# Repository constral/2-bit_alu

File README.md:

# 2-Bit Arithmetic Logic Unit with 4 Operations

<image src="picture.jpeg" width="800px"/>

## 1. Description

This 2-bit ALU (Arithmetic Logic Unit) is built using 74-series logic gates and multiplexers, and performs four basic operations: Logical AND, Logical OR, Addition, and positive-result Subtraction, on two 2-bit input words (A1A0 and B1B0). It uses a 2-bit opcode (I1I0) to select the operation, and displays the result as a 3-bit output (R2R1R0). Logical AND and OR operate only on the least significant bits (A0 and B0), with the result being displayed on R0. Arithmetic operations use the full words on input and output, and the output R2 is reserved for indicating overflow during addition.

## 2. Block Schematic
<image src="block.png" width="600px"/>

## 3. Logical Schematic and Simulation
Logisim Evolution was used for the prototyping of the circuit and for simulating its functionality. (file provided in repository)
<image src="logical.png" width="1000px"/>

## 4. Electrical Schematic and PCB
The project’s schematic and PCB were designed in KiCAD. (files provided in repository)
<image src="schematic.png" width="1000px"/>
<image src="pcb.png" width="800px"/>

## 5. Operation
The ALU takes two 2-bit words (A1A0 and B1B0) as input for its operations, and one 2-bit word (I1I0) for selecting the opcode. The results of the operations are displayed using LEDs in the form of a 3-bit word (R2R1R0). The operations and their opcodes are as follows:
<br>
<br>Logical AND		00
<br>Logical OR		01
<br>Addition		10
<br>Subtraction		11
<br>
<br>For the logical operations, only the least significant bits of the inputs - A0 and B0 - are operated upon, and the result is displayed on the result bit R0. The arithmetic operations employ the full 2-bit input word as well as two output bits, R1 and R0, while the third, R2, is reserved for displaying overflows from summations, and will remain LOW otherwise.

## 6. In-depth analysis of functionality
The general idea is that the input words A and B are forwarded to the operation-performing combinatorial logic gate circuits. Several multiplexers then select from among the results of the gate arrays, and based on the instruction opcode, the result of an operation is displayed. There are two arrays of multiplexers, corresponding to the 2-bit instruction word - I1 selects the arithmetic operations if 1, or the logic operations if 0. I0 further differentiates between the AND/OR, and SUM/DIFF operations.
<br>The logic unit is quite simple, being composed of just an AND and an OR gate, handling the AND and OR operations, respectively. Both gates are active at the same time - the desired result is chosen using a 2-input multiplexer.
<br>The arithmetic unit uses a 2-bit carry-lookahead adder (CLA for short) to perform addition and subtraction. The CLA adder works by taking 5 inputs - one for the carry-in of the summation of the LSB digits, as well as 4 more inputs consisting of the two 2-bit input words, A and B. The adder then outputs bits labeled to be the “sum” of each pair digits.

#### Timing considerations and adders
Generally, addition can be implemented with full adders, which work by taking as inputs two operators A, B, and a third input for the carry-in of the summation, and give as outputs one bit as the sum of the digits, and a second, which acts as the carry for a cascading summation. One full adder adds together one pair of digits, and many can be put in a cascading connection to produce a ripple-carry adder.
<br>Initially, the design of this ALU employed, for its arithmetic unit, two full adders with ripple carry, rather than a CLA adder. Upon further analysis, however, it was determined that the two full adders, which operated without any synchronicity signal from a clock (the only way of avoiding timing issues with such a design), would have produced wrong results due to timing issues caused by propagation delays inherent in the logic gates. A pseudo-timing diagram follows:
<image src="logi_wrong.png" width="1000px"/>
As can be seen from the schematic, the ripple-carry is sent from the first adder when the gate U4C fires its output, namely, in the 5th time period. This carry is meant to arrive at gate U3D – however, U3D fires in the 4th period, just before U4C, from which it is meant to receive its input. This is an obvious problem – U3D’s output will not account for the carry it was supposed to receive, since gate U4C had no time to send its output just yet.
<image src="logi_cla.png" width="1000px"/>
For a carry lookahead adder, however, no such issue exists – instead of waiting for the adders of less significant digits to finish their execution and send a ripple carry, the CLA adder uses extra logic circuitry that determines, based on the digits in the input words, whether a carry will be generated, before the adders dealing with said digits finish their execution. This absolves each individual adder of their dependency upon previous adder stages, allowing every individual pair to be summed up at the same time as, and without having to wait for, the others.
<br>The design principle of the CLA adder is the avoidance of successive propagation, by predicting whether an operation will give a carry, before the operation occurs in the first place. This is done by introducing extra logic gates into the design, accounting for all possible situations that could result in a stage receiving a carry. Whether one of the adder stages in a CLA adder receives a carry depends on whether a previous stage has either generated a carry by itself, or propagated one from a stage before it. This ALU implements a 2-bit CLA adder, so the situations that it accounts for w.r.t. each carry are:

Carry-out 0:
- do A0 and B0 generate a carry?
- is there a carry (generated externally) AND A0 and B0 propagate it?

Carry-out 1:
- do A1 and B1 generate a carry?
- is there a carry (generated by A0 and B0) AND A1 and B1 propagate it?
- is there a carry (generated externally) AND A0 and B0 propagate it AND A1 and B1 propagate it?

To further illustrate the principle, if we had to implement a 3-bit CLA adder, we would also have accounted for:

Carry-out 2:
- do A2 and B2 generate a carry?
- is there a carry (generated by A1 and B1) AND A2 and B2 propagate it?
- is there a carry (generated by A0 and B0) AND A1 and B1 propagate it AND A2 and B2 propagate it?
- is there a carry (generated externally) AND A0 and B0 propagate it AND A1 and B1 propagate it AND A2 and B2 propagate it?

... and so on, recursively, for any increase in width.
<br>
<br>A further consideration regarding timing issues would be the propagation delays caused by the lengths of the PCB route traces – in high frequency circuits, the signals must arrive at the same time to their destinations. However, this ALU was implemented without clock timing in mind, and as such, the PCB route lengths do not matter, because given enough time, all signals will arrive, and the output will eventually be displayed correctly.

#### Addition
In the addition mode, the first adder stage is a simple full adder, which starts with a carry-in of zero and adds the digits as normal. The “sum” output is sent to the result LED output R0, while the carry is used with look-ahead in mind for the addition of the second pair of digits.
<br>The second adder will similarly send the sum to the LED output on R1, but the process is slightly modified, and also, the carry-out of this stage will have accounted for the carry-out of the first adder, by checking all possible situations. 
<br>Since there is no third adder for the second carry-out to cascade to, any potential overflow will need to be displayed in order to produce the accurate result of the summation. The output R2 has been designated for this, and for all other situations, a circuit using two logic gates has been put in place to keep the state of R2 low.

#### Subtraction
Binary subtraction is performed using the two’s complement summation. This requires computing the two’s complement of the B input, which is done by inverting the digits of B and adding 1. For instance, for a B = 01, the two’s complement is obtained by inverting B, giving us “10”, and adding 1. Thus we have: 10 + 01 = 11.
<br>The inversion of B can be done by applying inverters to each of B’s digits, this being implemented using NAND gates that are tied to B’s normal values. Seeing as addition and subtraction require the normal and the inverted values of B respectively, two multiplexers are used to select from among them, depending on the desired operation.
<br>In the case of 2-bit operands, binary subtraction of A and the two’s complement of B therefore means:
<br>
<br>A1 A0 +
<br>B1’B0’+
<br>0  1
<br>
<br>With the normal inputs of A, as well as the inverted B which is selectable by the multiplexers, all that remains is providing an additional 1 to the summation. This can be conveniently done by passing the carry-in to the addition of A0 and B0 as 1 whenever subtraction is chosen as the operation; the carry-in would otherwise remain 0 when addition is performed. It so happens that the instruction bit I0 behaves exactly in this manner, allowing us to use it as the carry-in to the first adder stage.
<br>It should be noted that the subtraction operation comes with some inherent caveats due to its employment of the two’s complement. For instance, without the logic gates that condition the output R2 solely to display the overflow of addition operations, the subtraction operation - itself employing summations, potentially overflowing - would also display overflows on the pin. The logic gates fix this, and the outputs on the other two LEDs are otherwise correct, if no overflow is displayed on R2.
<br>Another functional incompleteness is found when performing subtractions that would give negative results. For instance, the operation 00 - 11 gives the result 100. Even without accounting for the output on R2, we can see how this is actually an integer overflow, arising as the result of 111 - 11. So, because we have no way of converting such overflows, nor otherwise handling signed integers, subtraction operations resulting in negative-signed results are completely unsupported by the circuit and will give an incorrect result.

## 7. Bill of Materials
SMD ICs:
- NAND:	1x MM74HC00M (SO-14)
- AND:	2x MM74HC08M (SO-14)
- OR:	1x MM74HC32M (SO-14)
- XOR:	1x MM74HC86M (SO-14)
- MUX:	2x SN74LS157D (SO-16)

Other components, THT:
- 3x LEDs
- 3x 470Ω resistors
- 8x 1kΩ resistors
- 1x 10uF electrolytic capacitor
- 1x 10nF ceramic capacitor
- 1x 2-pin female socket connector

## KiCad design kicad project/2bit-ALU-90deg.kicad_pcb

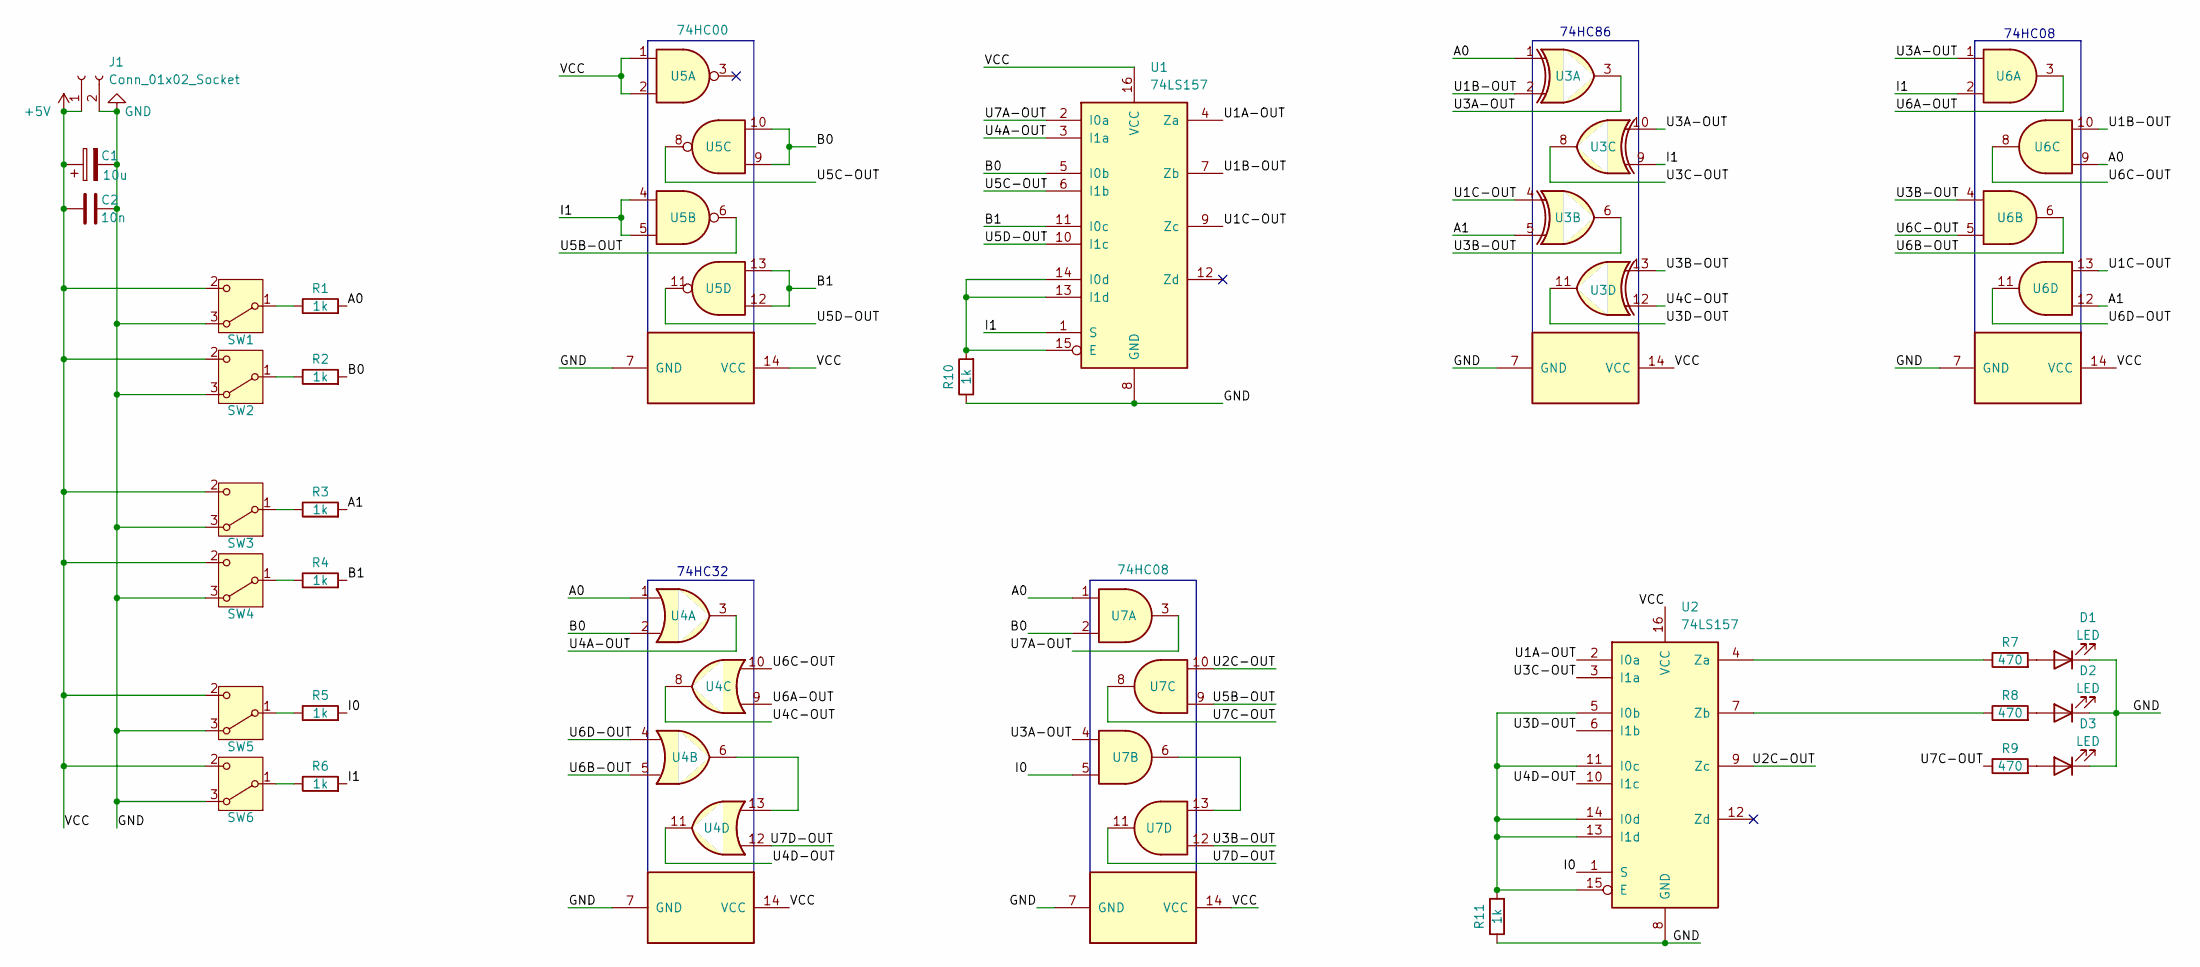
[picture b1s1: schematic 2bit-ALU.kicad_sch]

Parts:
C1: 10u; CP_Radial_D5.0mm_P2.50mm
C2: 10n; C_Disc_D3.0mm_W2.0mm_P2.50mm
D1, D2, D3: LED; LED_D5.0mm_Clear
J1: Conn_01x02_Socket; PinSocket_1x02_P2.00mm_Vertical
R1, R2, R3, R4, R5, R6, R10, R11: 1k; R_Axial_DIN0204_L3.6mm_D1.6mm_P7.62mm_Horizontal
R7, R8, R9: 470; R_Axial_DIN0204_L3.6mm_D1.6mm_P7.62mm_Horizontal
SW1, SW2, SW3, SW4, SW5, SW6: SW_Wuerth_450301014042; SW_Slide-03_Wuerth-WS-SLTV_10x2.5x6.4_P2.54mm
U1, U2: 74LS157; SO-16_3.9x9.9mm_P1.27mm
U3: 74HC86; SO-14_3.9x8.65mm_P1.27mm
U4: 74LS32; SO-14_3.9x8.65mm_P1.27mm
U5: 74HC00; SO-14_3.9x8.65mm_P1.27mm
U6: 74LS08; SO-14_3.9x8.65mm_P1.27mm
U7: 74HC08; SO-14_3.9x8.65mm_P1.27mm

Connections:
+5V: C1.1, C2.1, J1.1, SW1.2 (C), SW2.2 (C), SW3.2 (C), SW4.2 (C), SW5.2 (C), SW6.2 (C), U1.16 (VCC), U2.16 (VCC), U3.14 (VCC), U4.14 (VCC), U5.1, U5.2, U5.14 (VCC), U6.14 (VCC), U7.14 (VCC)
/A0: R1.2, U3.1, U4.1, U6.9, U7.1
/A1: R3.2, U3.5, U6.12
/B0: R2.2, U1.5 (I0b), U4.2, U5.9, U5.10, U7.2
/B1: R4.2, U1.11 (I0c), U5.12, U5.13
/I0: R5.2, U2.1 (S), U7.5
/I1: R6.2, U1.1 (S), U3.9, U5.4, U5.5, U6.2
/U1A-OUT: U1.4 (Za), U2.2 (I0a)
/U1B-OUT: U1.7 (Zb), U3.2, U6.10
/U1C-OUT: U1.9 (Zc), U3.4, U6.13
/U2C-OUT: U2.9 (Zc), U7.10
/U3A-OUT: U3.3, U3.10, U6.1, U7.4
/U3B-OUT: U3.6, U3.13, U6.4, U7.12
/U3C-OUT: U2.3 (I1a), U3.8
/U3D-OUT: U2.6 (I1b), U3.11
/U4A-OUT: U1.3 (I1a), U4.3
/U4C-OUT: U3.12, U4.8
/U4D-OUT: U2.10 (I1c), U4.11
/U5B-OUT: U5.6, U7.9
/U5C-OUT: U1.6 (I1b), U5.8
/U5D-OUT: U1.10 (I1c), U5.11
/U6A-OUT: U4.9, U6.3
/U6B-OUT: U4.5, U6.6
/U6C-OUT: U4.10, U6.5, U6.8
/U6D-OUT: U4.4, U6.11
/U7A-OUT: U1.2 (I0a), U7.3
/U7C-OUT: R9.1, U7.8
/U7D-OUT: U4.12, U7.11
GND: C1.2, C2.2, D1.1 (K), D2.1 (K), D3.1 (K), J1.2, R10.1, R11.1, SW1.3 (A), SW2.3 (A), SW3.3 (A), SW4.3 (A), SW5.3 (A), SW6.3 (A), U1.8 (GND), U2.8 (GND), U3.7 (GND), U4.7 (GND), U5.7 (GND), U6.7 (GND), U7.7 (GND)
unnamed: D1.2 (A), R7.2
unnamed: D2.2 (A), R8.2
unnamed: D3.2 (A), R9.2
unnamed: R1.1, SW1.1 (B)
unnamed: R2.1, SW2.1 (B)
unnamed: R3.1, SW3.1 (B)
unnamed: R4.1, SW4.1 (B)
unnamed: R5.1, SW5.1 (B)
unnamed: R6.1, SW6.1 (B)
unnamed: R10.2, U1.13 (I1d), U1.14 (I0d), U1.15 (E)
unnamed: R11.2, U2.5 (I0b), U2.11 (I0c), U2.13 (I1d), U2.14 (I0d), U2.15 (E)
unnamed: R7.1, U2.4 (Za)
unnamed: R8.1, U2.7 (Zb)
unnamed: U4.6, U4.13
unnamed: U7.6, U7.13

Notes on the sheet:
74HC32
74HC08
74HC86

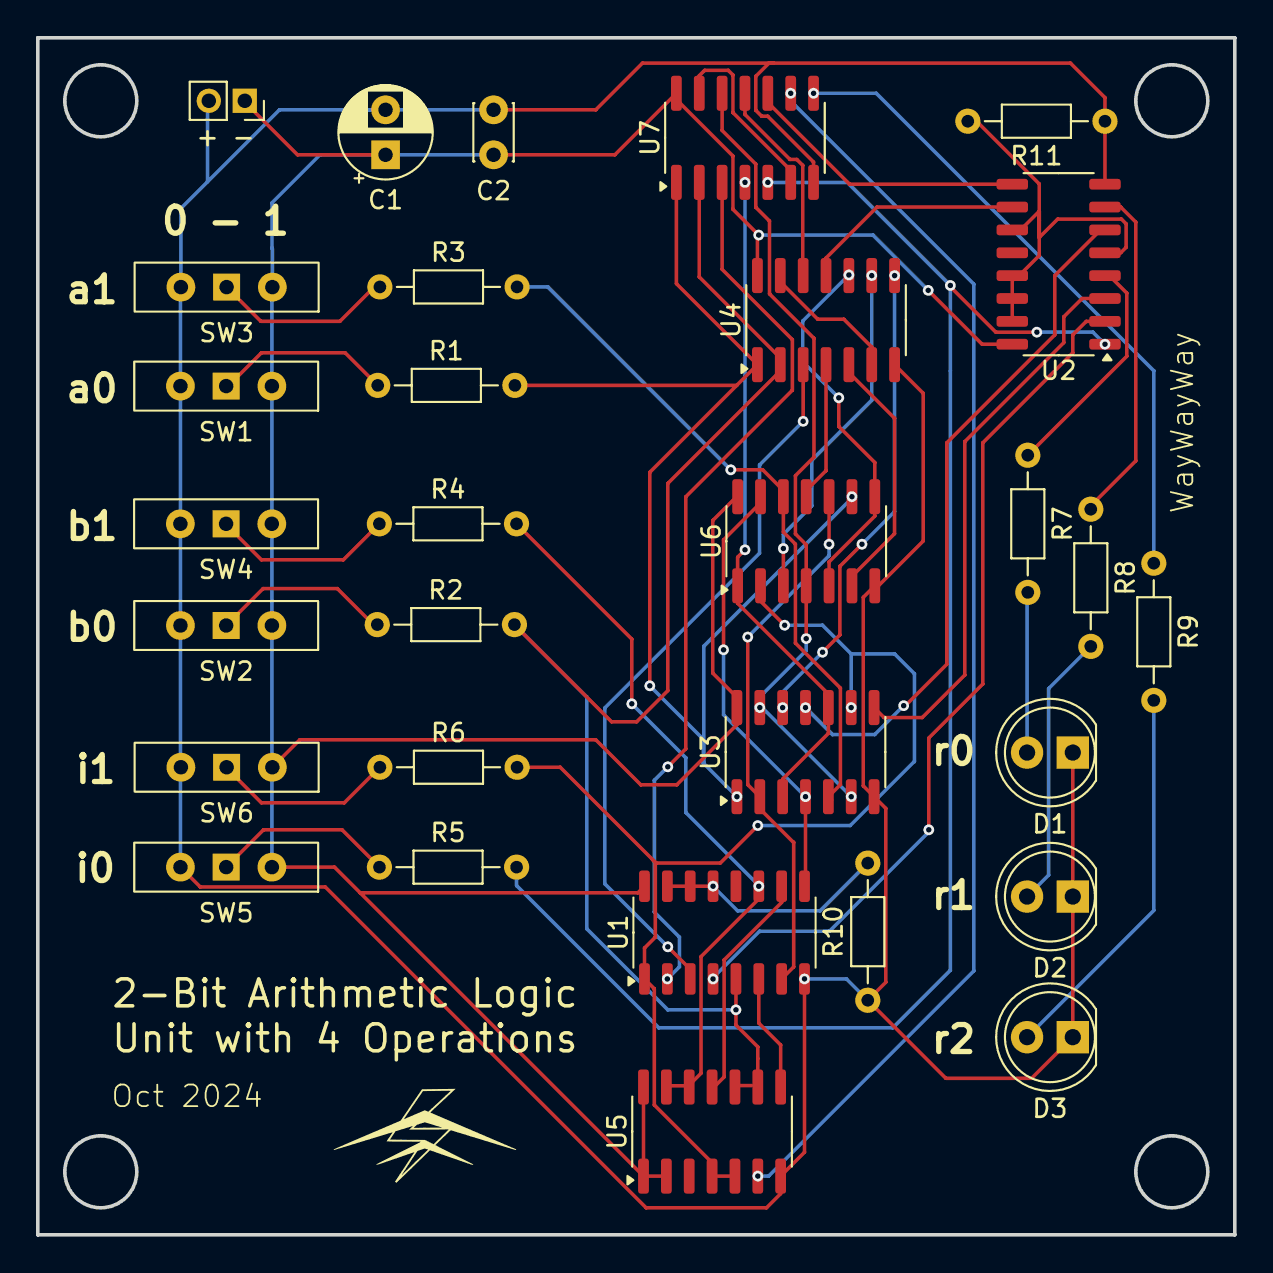
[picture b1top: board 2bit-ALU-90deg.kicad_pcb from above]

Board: 2 copper layers, 66.5 x 66.5 mm, 30 parts (0 on the bottom side), 44 nets.

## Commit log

2024-11-20 created
2024-11-20 added circuit files
2024-12-03 added picture
